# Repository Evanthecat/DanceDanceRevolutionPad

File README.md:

# DanceDanceRevolutionPad
This is a simple keypad that I made for Dance Dance Revolution similar games, like Friday Night Funkin' and the Lightner's Live minigame in Deltarune. It has a small 128x64 OLED display, 11 keys, and a knob for changing the keybinds.

# PCB

# Case
The case consists of three parts: the base, the top plate (to hold the switches/PCB to the case), and the cover plate (to cover all the components and make it look nicer).

The parts should fit on top of each other and can be held together with four M3x5mx4mm heatset inserts and M3x16mm screws.

# BOM
The materials needed for this HackPad are listed below:
- 11x Cherry MX Switches
- 11x White blank DSA keycaps
- 1x 0.91 Inch OLED display
- 1x Seeed XIAO RP2040
- 1x EC11E Rotary encoder
- 4x M3x16mm Screws
- 4x M3x5mx4mm Heatset inserts
- 1x Case (should be three 3D printed parts)
- 1x 3D printed knob
- 1x Custom PCB

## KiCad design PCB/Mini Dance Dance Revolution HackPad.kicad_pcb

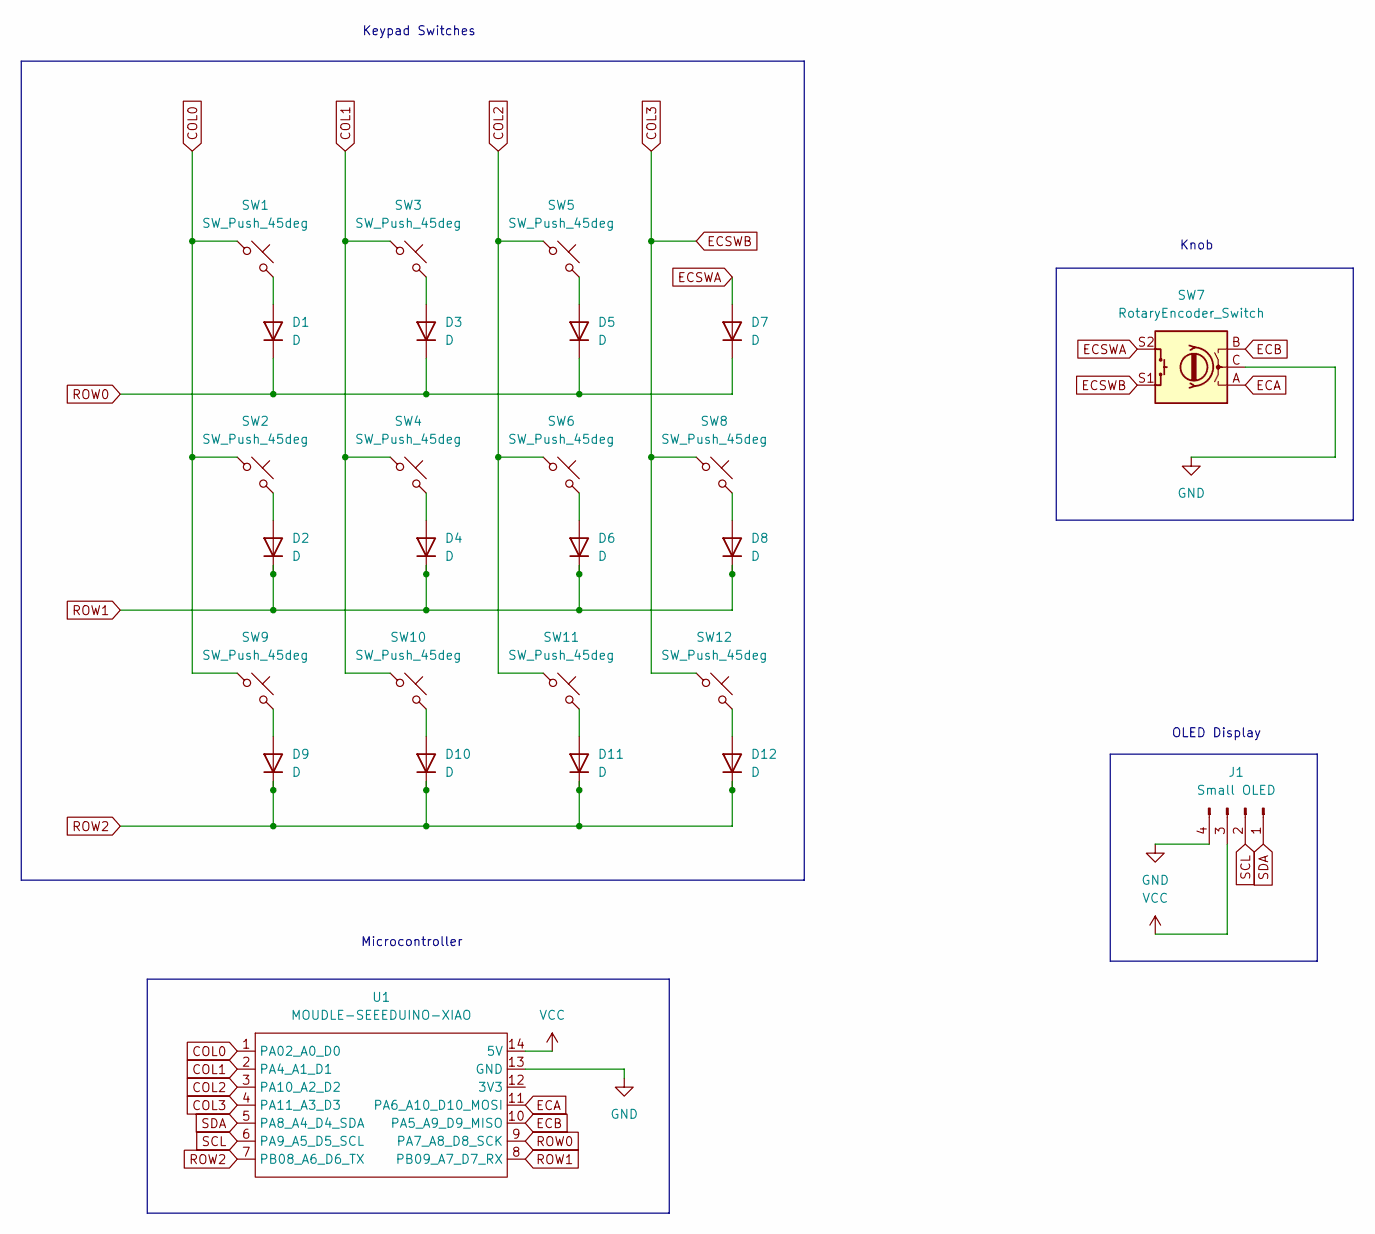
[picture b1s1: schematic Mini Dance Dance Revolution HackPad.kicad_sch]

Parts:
D1, D2, D3, D4, D5, D6, D7, D8, D9, D10, D11, D12: D; D_DO-35_SOD27_P7.62mm_Horizontal
J1: Small OLED; SSD1306-0.91-OLED-4pin-128x32
SW1, SW2, SW3, SW4, SW5, SW6, SW8, SW9, SW10, SW11, SW12: SW_Push_45deg; SW_Cherry_MX_1.00u_PCB
SW7: RotaryEncoder_Switch; RotaryEncoder_Alps_EC11E-Switch_Vertical_H20mm
U1: MOUDLE-SEEEDUINO-XIAO; XIAO-Generic-Hybrid-14P-2.54-21X17.8MM

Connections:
COL0: SW1.1, SW2.1, SW9.1, U1.1 (PA02_A0_D0)
COL1: SW3.1, SW4.1, SW10.1, U1.2 (PA4_A1_D1)
COL2: SW5.1, SW6.1, SW11.1, U1.3 (PA10_A2_D2)
COL3: SW7.S1, SW8.1, SW12.1, U1.4 (PA11_A3_D3)
ECA: SW7.A, U1.11 (PA6_A10_D10_MOSI)
ECB: SW7.B, U1.10 (PA5_A9_D9_MISO)
ECSWA: D7.2 (A), SW7.S2
GND: J1.4, SW7.C, U1.13 (GND)
unnamed: D1.2 (A), SW1.2
unnamed: D2.2 (A), SW2.2
unnamed: D3.2 (A), SW3.2
unnamed: D4.2 (A), SW4.2
unnamed: D5.2 (A), SW5.2
unnamed: D6.2 (A), SW6.2
unnamed: D8.2 (A), SW8.2
unnamed: D9.2 (A), SW9.2
unnamed: D10.2 (A), SW10.2
unnamed: D11.2 (A), SW11.2
unnamed: D12.2 (A), SW12.2
ROW0: D1.1 (K), D3.1 (K), D5.1 (K), D7.1 (K), U1.9 (PA7_A8_D8_SCK)
ROW1: D2.1 (K), D4.1 (K), D6.1 (K), D8.1 (K), U1.8 (PB09_A7_D7_RX)
ROW2: D9.1 (K), D10.1 (K), D11.1 (K), D12.1 (K), U1.7 (PB08_A6_D6_TX)
SCL: J1.2, U1.6 (PA9_A5_D5_SCL)
SDA: J1.1, U1.5 (PA8_A4_D4_SDA)
VCC: J1.3, U1.14 (5V)

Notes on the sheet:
Microcontroller
Keypad Switches
Knob
OLED Display

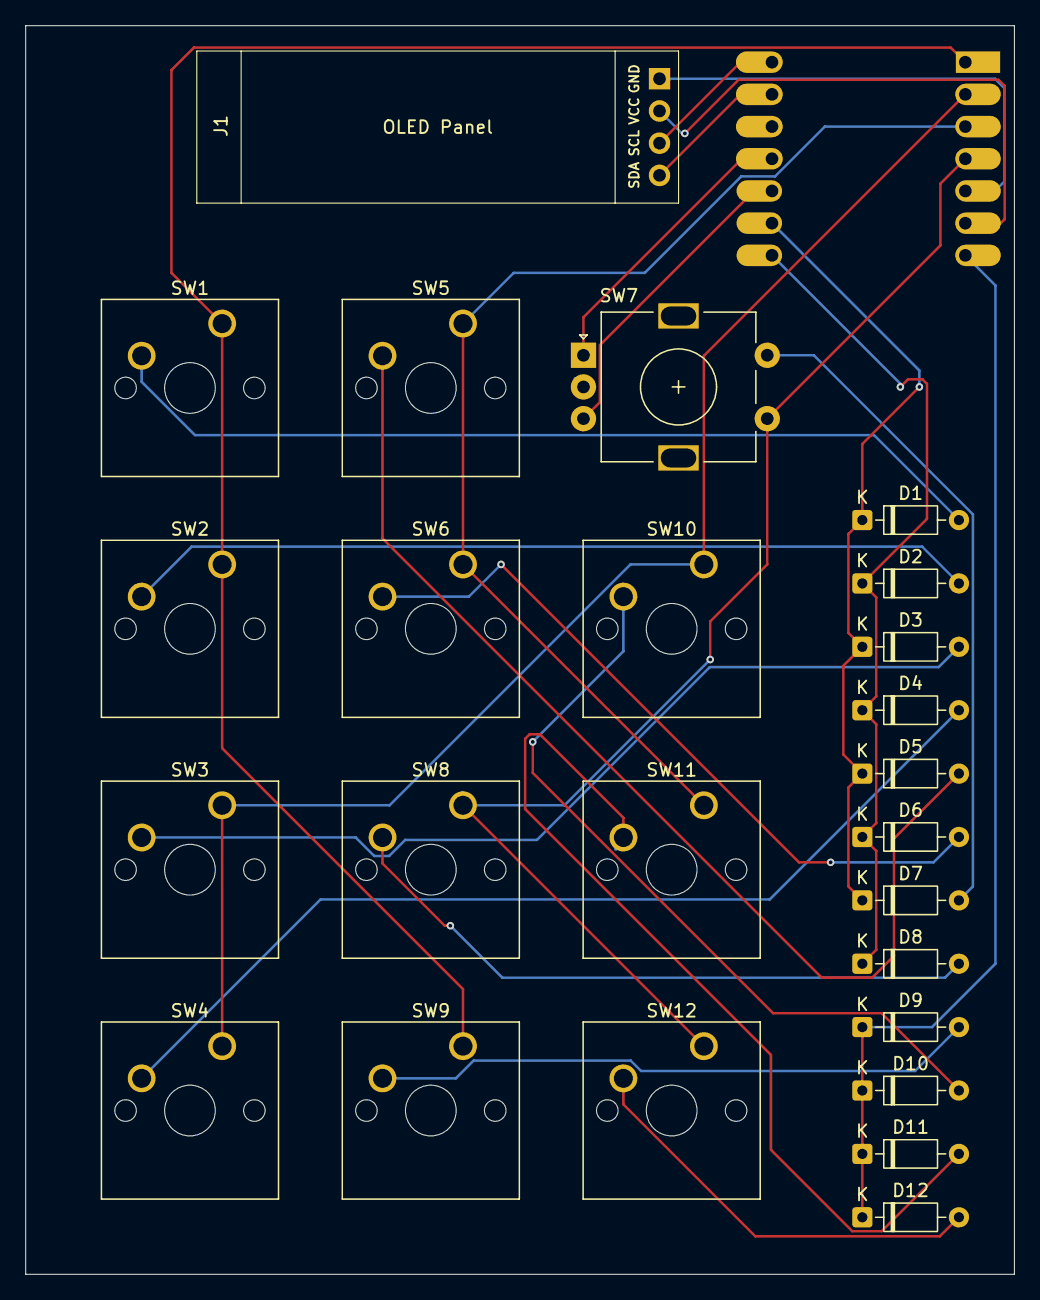
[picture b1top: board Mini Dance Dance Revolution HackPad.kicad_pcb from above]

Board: 2 copper layers, 78.0 x 98.5 mm, 26 parts (1 on the bottom side), 25 nets.
